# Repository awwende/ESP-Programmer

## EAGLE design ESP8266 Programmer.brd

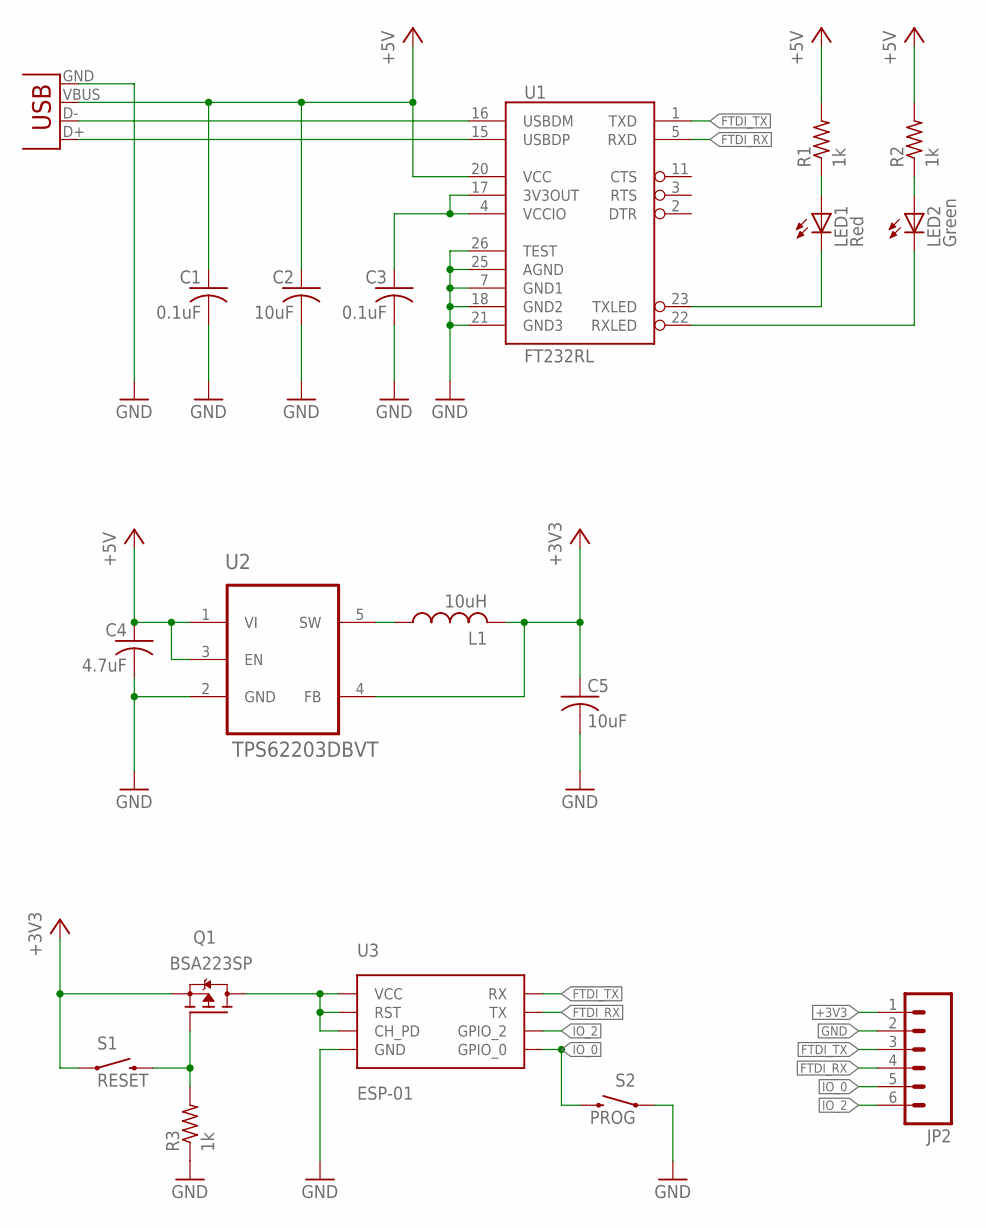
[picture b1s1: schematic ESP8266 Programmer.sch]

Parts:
C1, C3: 0.1uF; C0603
C2, C5: 10uF; C0603
C4: 4.7uF; C0603
JP1: USBSMD; USB-MINIB
JP2: M06NO_SILK; 1X06_NO_SILK
L1: 10uH; L0806
LED1: Red; CHIPLED_0805
LED2: Green; CHIPLED_0805
Q1: BSA223SP; SC75_INFINEON
R1, R2, R3: 1k; R0603
S1: RESET; TACTILE_SWITCH_TALL
S2: PROG; TACTILE_SWITCH_TALL
U1: FT232RL; SSOP28DB
U2: TPS62203DBVT; SOT95P280X145-5N
U3: ESP-01

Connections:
+3V3: C5.1, JP2.1, L1.2, Q1.3 (S), S1.A2 (1), U2.4 (FB)
+5V: C1.1, C2.1, C4.1, JP1.VBUS, R1.2, R2.2, U1.20 (VCC), U2.1 (VI), U2.3 (EN)
FTDI_RX: JP2.4, U1.5 (RXD), U3.TX
FTDI_TX: JP2.3, U1.1 (TXD), U3.RX
GND: C1.2, C2.2, C3.2, C4.2, C5.2, JP1.GND, JP2.2, R3.1, S2.A2 (1), U1.7 (GND1), U1.18 (GND2), U1.21 (GND3), U1.25 (AGND), U1.26 (TEST), U2.2 (GND), U3.GND
IO_0: JP2.5, S2.B2 (2), U3.GPIO_0
IO_2: JP2.6, U3.GPIO_2
unnamed: JP1.D-, U1.16 (USBDM)
unnamed: JP1.D+, U1.15 (USBDP)
unnamed: Q1.2 (D), U3.CH_PD, U3.RST, U3.VCC
unnamed: C3.1, U1.4 (VCCIO), U1.17 (3V3OUT)
unnamed: L1.1, U2.5 (SW)
unnamed: LED1.C, U1.23 (TXLED)
unnamed: LED2.C, U1.22 (RXLED)
unnamed: Q1.1 (G), R3.2, S1.B2 (2)
unnamed: LED1.A, R1.1
unnamed: LED2.A, R2.1

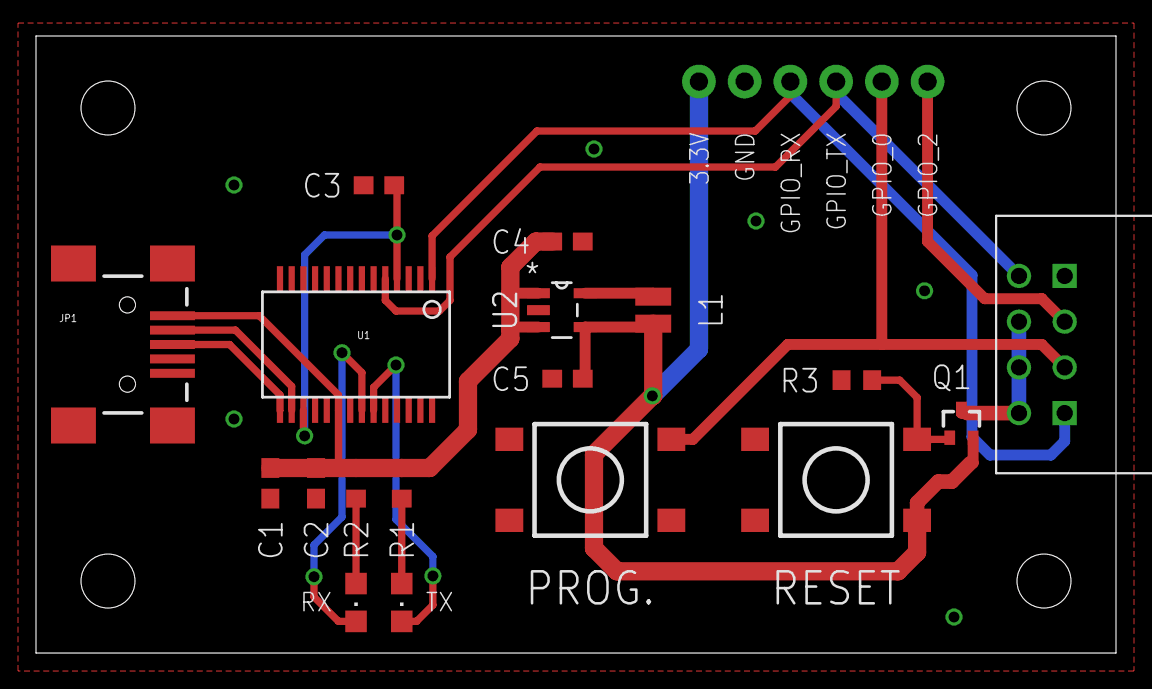
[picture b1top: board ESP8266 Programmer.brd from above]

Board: 2 copper layers, 60.0 x 34.3 mm, 19 parts (0 on the bottom side), 17 nets.

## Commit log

2015-11-13 :boom::camel: Added .gitattributes & .gitignore files
2015-11-13 Initial Release

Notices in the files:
parts and their libraries:
SparkFun-DigitalIC: Licensing: Creative Commons ShareAlike 4.0 International - https://creativecommons.org/licenses/by-sa/4.0
